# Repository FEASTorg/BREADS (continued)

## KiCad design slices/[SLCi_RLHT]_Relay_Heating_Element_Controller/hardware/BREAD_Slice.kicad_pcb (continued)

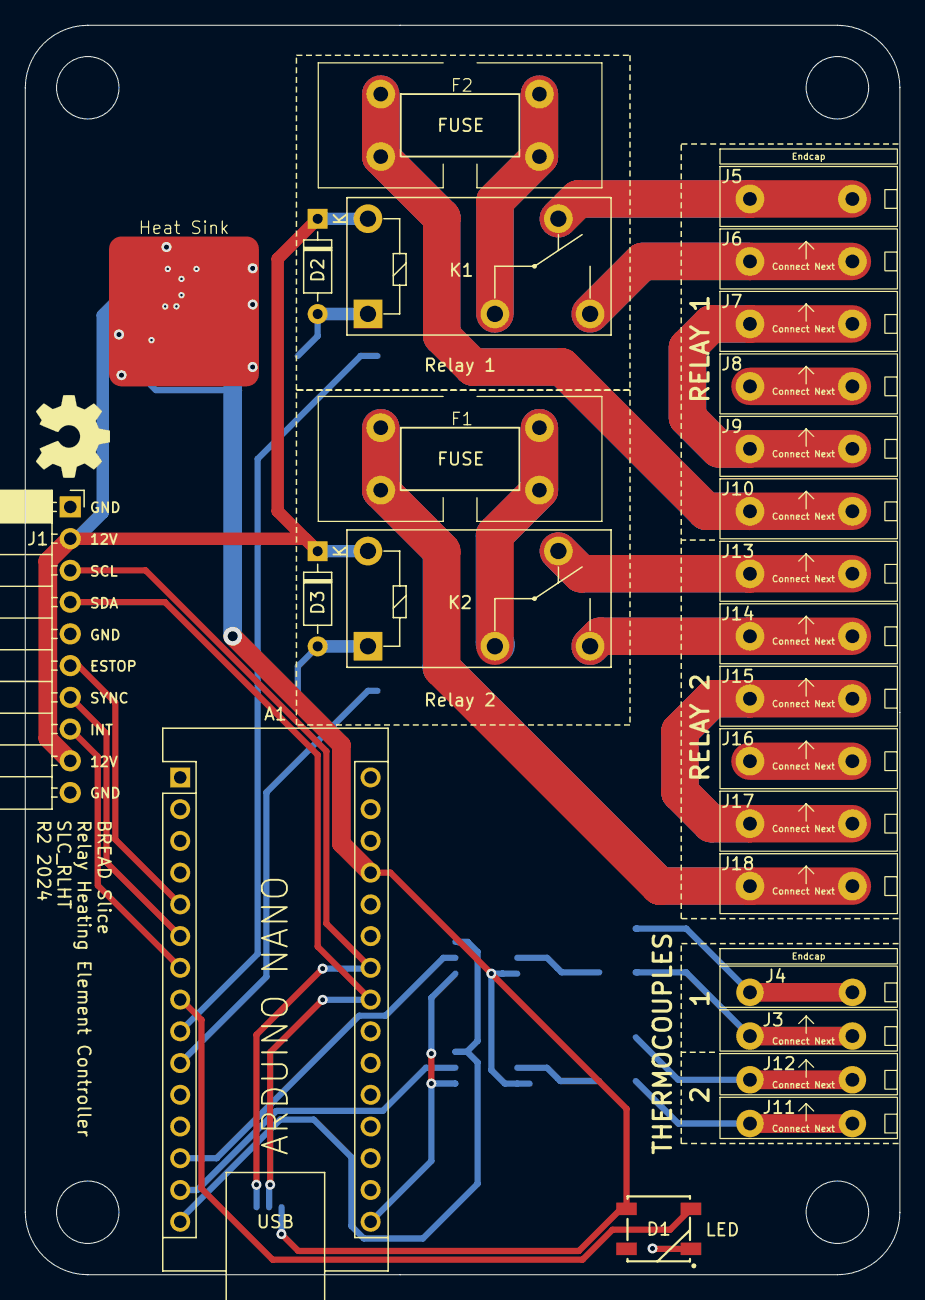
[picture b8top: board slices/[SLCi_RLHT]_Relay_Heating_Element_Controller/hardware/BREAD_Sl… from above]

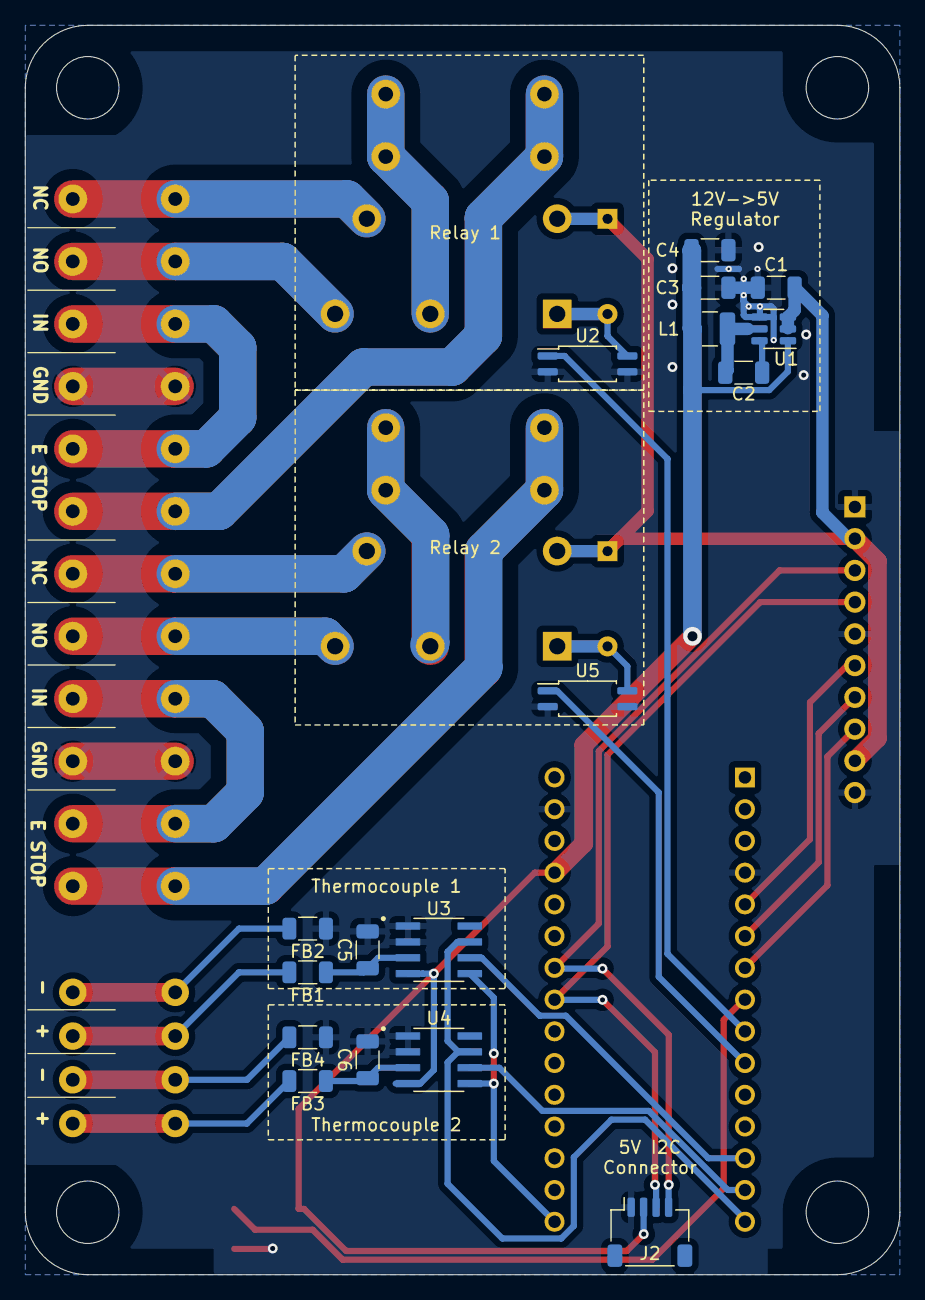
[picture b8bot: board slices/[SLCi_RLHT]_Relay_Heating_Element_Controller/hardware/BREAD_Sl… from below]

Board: 2 copper layers, 70.0 x 100.0 mm, 48 parts (17 on the bottom side), 35 nets.

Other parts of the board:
Logo1: Logo_Open_Hardware_Small; OSHW-Symbol_6.7x6mm_SilkScreen
